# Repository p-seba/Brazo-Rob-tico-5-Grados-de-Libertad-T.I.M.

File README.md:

# Brazo Robótico de 5 Grados de Libertad - T.I.M.
Proyecto del Taller Inicial de Mecatrónica, Facultad de Ingeniería, UNCuyo. 

En este repositorio encontrarás todos los archivos asociados a la realización y presentación final del proyecto.    

Aplicaciones utilizadas: 
* Autodesk Fusion
* KiCad
* Visual Studio Code (PlatformIO)

En la carpeta de **Código** se encuentra una recopilación de todos los programas utilizados durante las pruebas y el código final. 

En la carpeta de **Diseño 3D** están los archivos de modelado y dos renders. Todo el diseño fue realizado por el grupo, excepto por el componente de la garra, el cual es una modificación del diseño original de **Julián Herrera**, disponible en: https://grabcad.com/library/gripper-and-servo-mg90s-1 

En la carpeta **PCB** están subidos los archivos de KiCad utilizados para diseñar las conexiones finales.  

En la carpeta **Documentación** están subidos todos los trabajos prácticos asociados a la materia y el informe final presentado en la mesa de examen. 

## Enlaces de interés 

* **Diseño en Fusion:** https://a360.co/4xZ3YgB 
* **Informe:** 

### Herramientas:
* **Autodesk Fusion:** https://www.autodesk.com/latam/products/fusion-360/overview
* **KiCad:** https://www.kicad.org/
* **Visual Studio Code:** https://code.visualstudio.com/
* **PlatformIO:** https://platformio.org/

---
Ante cualquier consulta, contactar a: joaquin.winckler@gmail.com

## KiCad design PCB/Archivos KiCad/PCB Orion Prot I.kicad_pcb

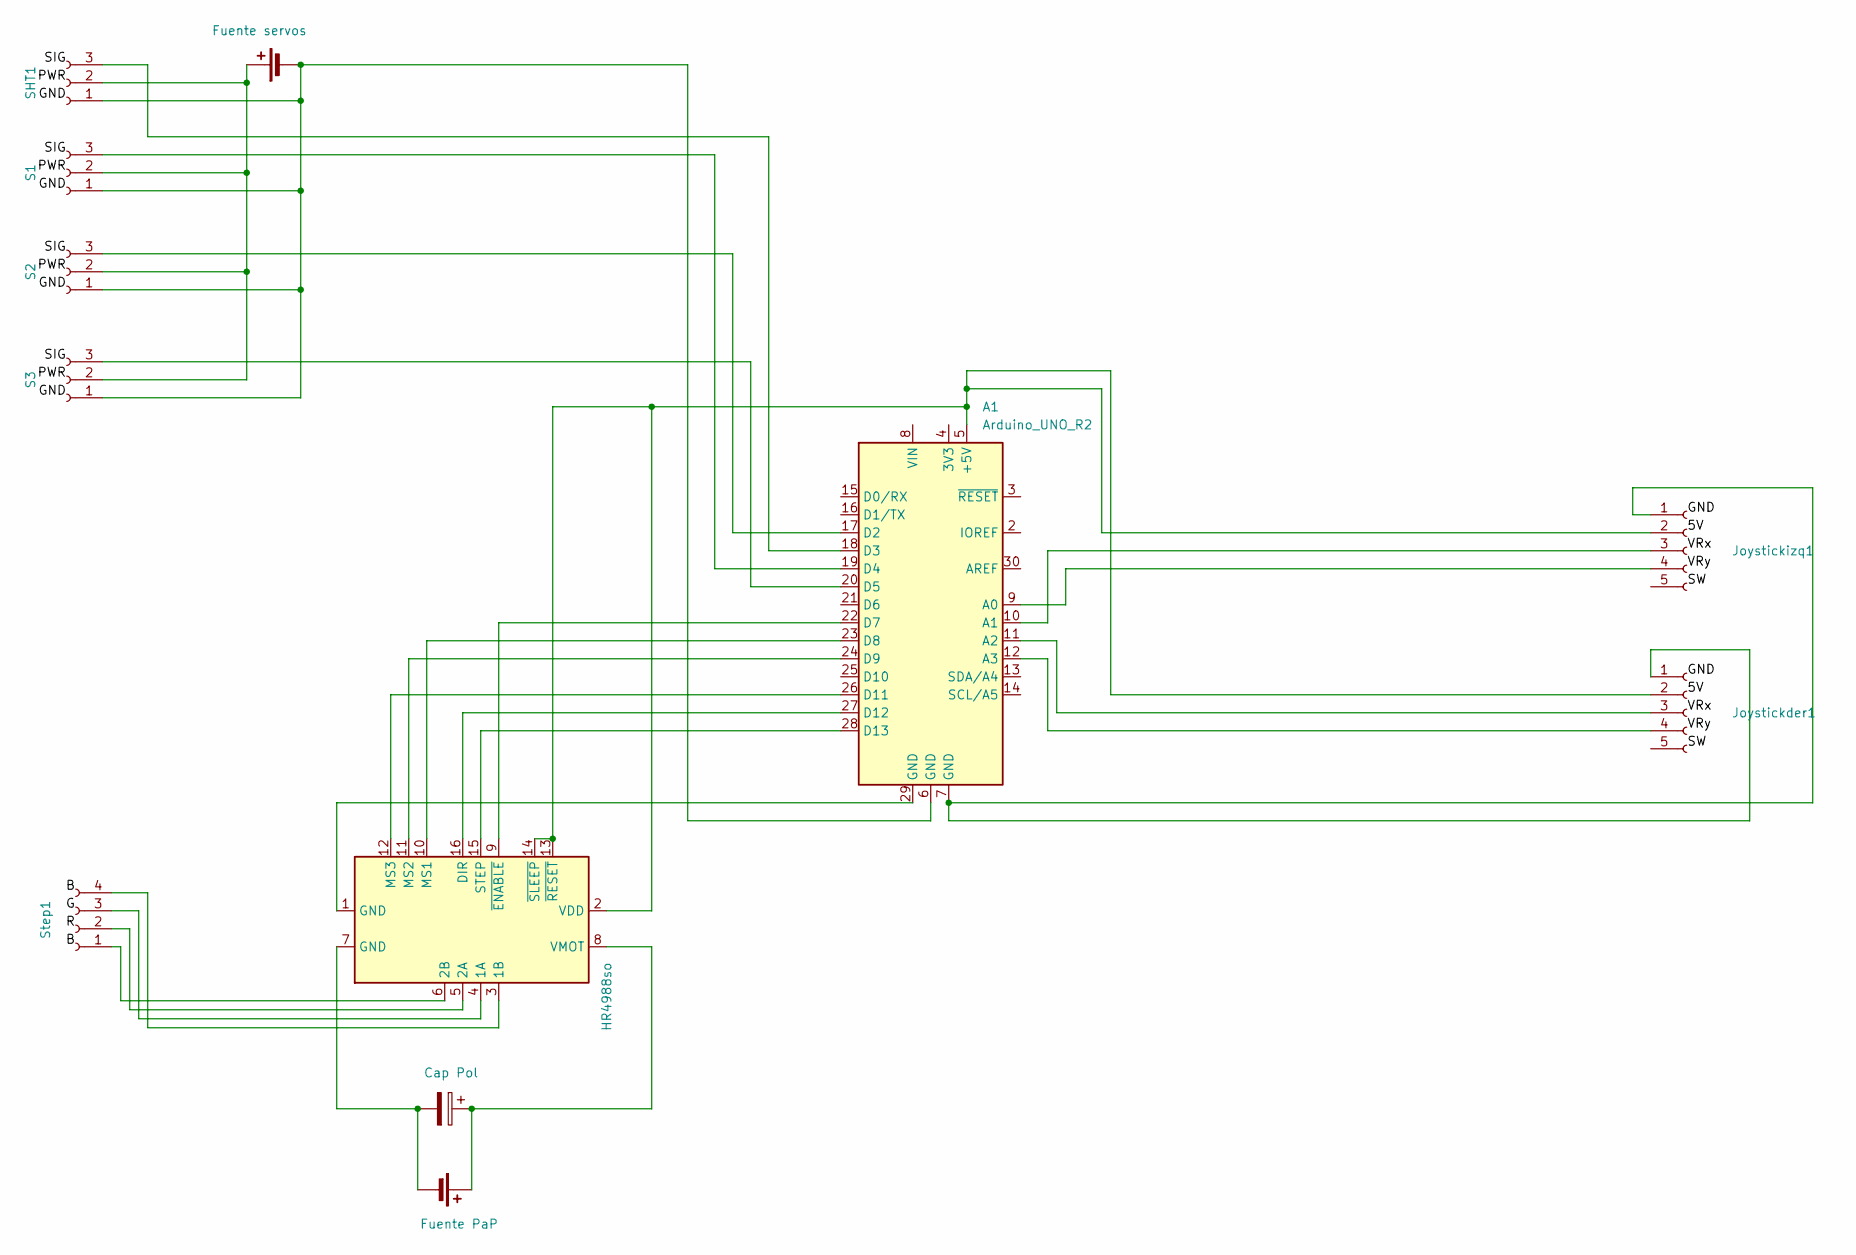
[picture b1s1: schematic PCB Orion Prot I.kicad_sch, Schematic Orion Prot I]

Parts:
A1: Arduino_UNO_R2
A2: HR4988so; Pololu_Breakout-16_15.2x20.3mm
BT1: Fuente servos; TerminalBlock_MaiXu_MX126-5.0-02P_1x02_P5.00mm
BT2: Fuente PaP; TerminalBlock_MaiXu_MX126-5.0-02P_1x02_P5.00mm
C2: Cap Pol; CP_Radial_D8.0mm_P3.50mm
Joystickder1: Conn_01x05_Socket; PinSocket_1x05_P2.54mm_Vertical
Joystickizq1: Conn_01x05_Socket; PinSocket_1x05_P2.54mm_Vertical
S1, S2, S3: Conn_01x03_Socket; PinHeader_1x03_P2.54mm_Vertical
SHT1: Conn_01x03_Socket; PinHeader_1x03_P2.54mm_Vertical
Step1: Conn_01x04_Socket; TerminalBlock_MaiXu_MX126-5.0-04P_1x04_P5.00mm

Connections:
unnamed: A1.5 (+5V), A2.2 (VDD), A2.13 (~RESET), A2.14 (~SLEEP), Joystickder1.2, Joystickizq1.2
unnamed: A1.9 (A0), Joystickizq1.4
unnamed: A1.10 (A1), Joystickizq1.3
unnamed: A1.11 (A2), Joystickder1.3
unnamed: A1.12 (A3), Joystickder1.4
unnamed: A1.17 (D2), S2.3
unnamed: A1.18 (D3), SHT1.3
unnamed: A1.19 (D4), S1.3
unnamed: A1.20 (D5), S3.3
unnamed: A1.22 (D7), A2.9 (~ENABLE)
unnamed: A1.23 (D8), A2.10 (MS1)
unnamed: A1.24 (D9), A2.11 (MS2)
unnamed: A1.26 (D11), A2.12 (MS3)
unnamed: A1.27 (D12), A2.16 (DIR)
unnamed: A1.28 (D13), A2.15 (STEP)
unnamed: A1.29 (GND), A2.1 (GND)
unnamed: A2.4 (1A), Step1.3
unnamed: A2.3 (1B), Step1.4
unnamed: A2.5 (2A), Step1.2
unnamed: A2.6 (2B), Step1.1
unnamed: A2.8 (VMOT), BT2.1 (+), C2.1
unnamed: BT1.1 (+), S1.2, S2.2, S3.2, SHT1.2
unnamed: A1.6 (GND), BT1.2 (-), S1.1, S2.1, S3.1, SHT1.1
unnamed: A2.7 (GND), BT2.2 (-), C2.2
unnamed: A1.7 (GND), Joystickder1.1, Joystickizq1.1

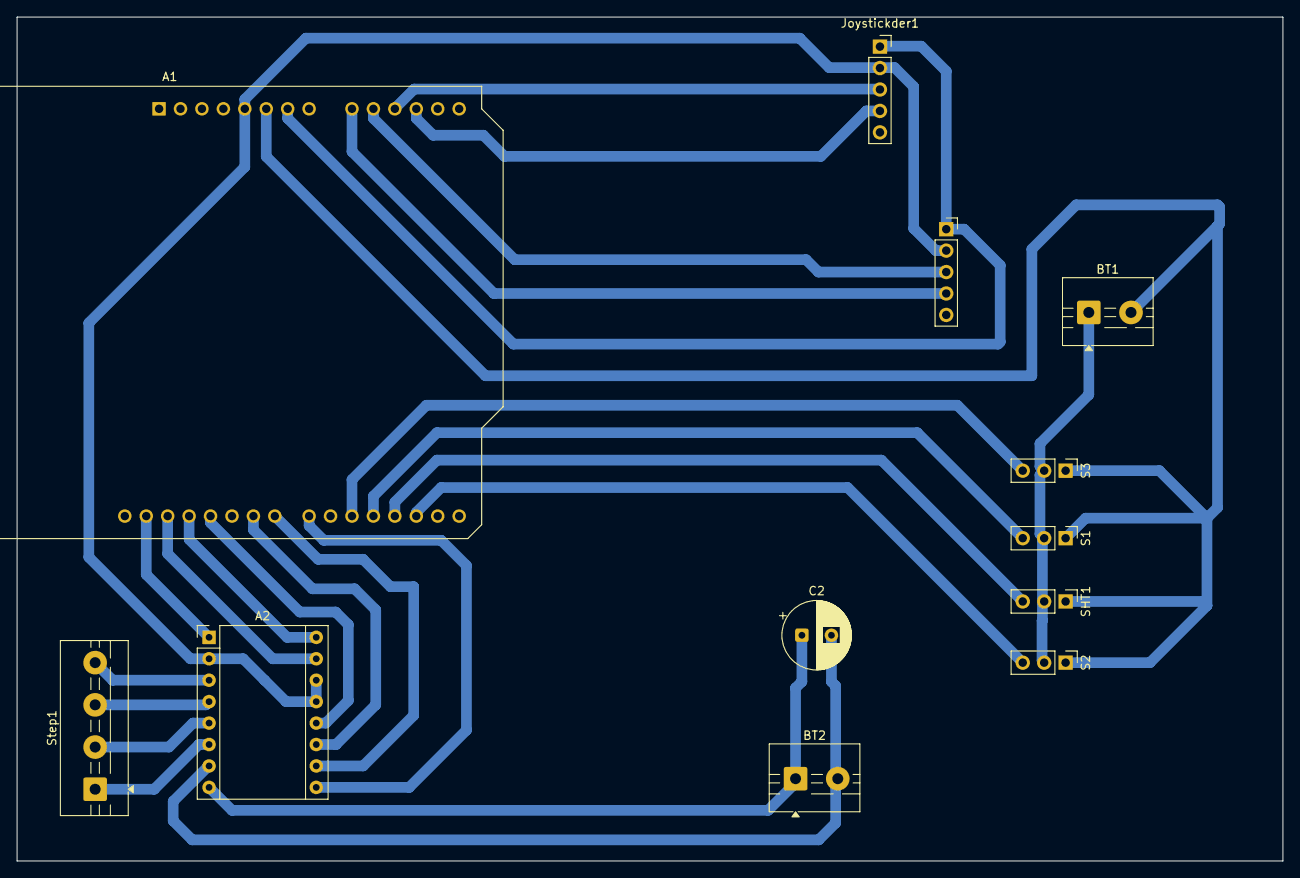
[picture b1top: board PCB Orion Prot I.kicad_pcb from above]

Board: 2 copper layers, 150.0 x 100.0 mm, 12 parts (0 on the bottom side), 25 nets.

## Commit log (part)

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2026-06-30 Debug final
    Código utilizado para encontrar error en el valor final de los joysticks.
2026-06-30 Debug
2026-06-30 Codigo final
